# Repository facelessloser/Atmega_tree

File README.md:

# Atmega_tree
Xmas decoration powered by a atmega328 with a few ws2812 LED's

WS2812 library - https://github.com/cpldcpu/light_ws2812

Hardware walk thought - https://youtu.be/ifKlebYnPPQ

Blog post - https://facelesstech.wordpress.com/2015/12/17/atmega_tree/

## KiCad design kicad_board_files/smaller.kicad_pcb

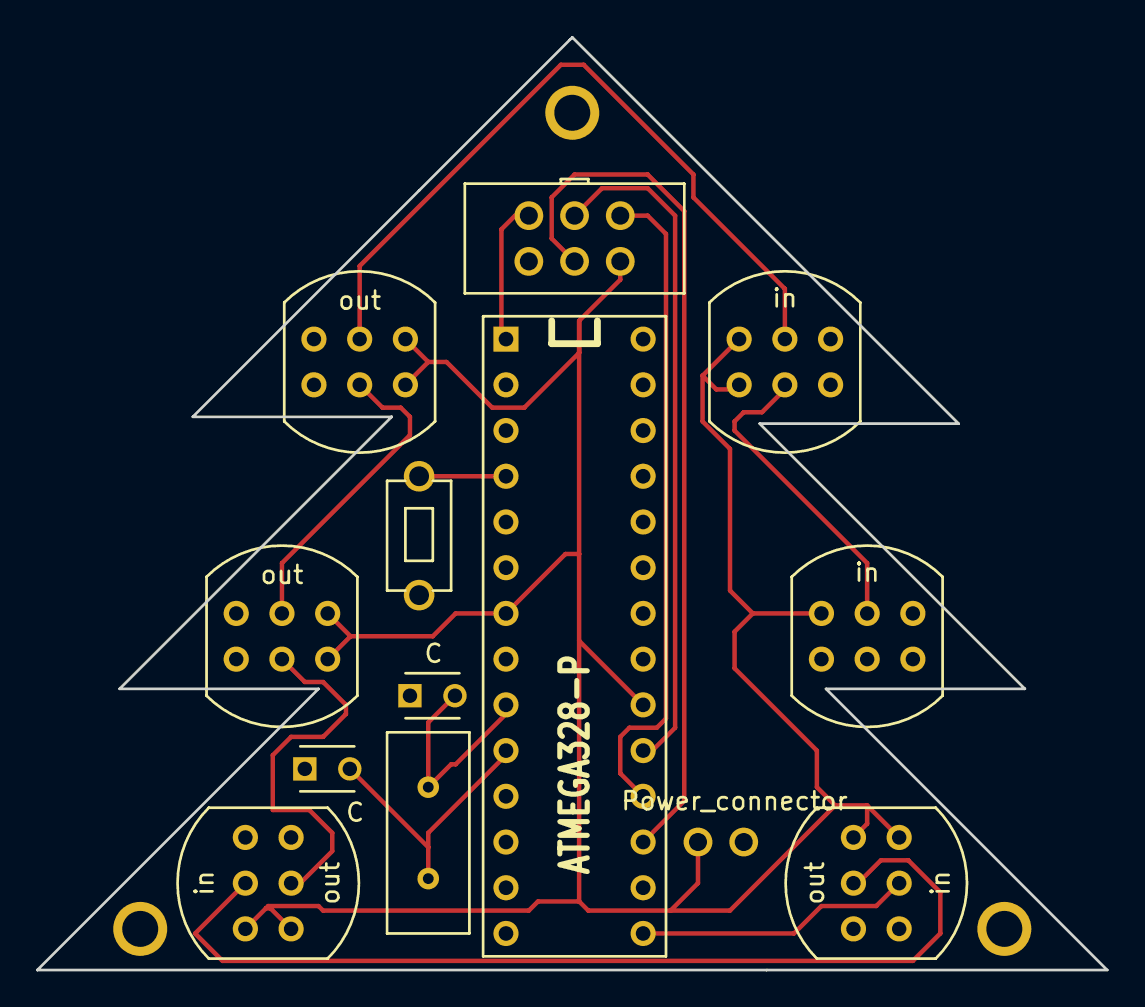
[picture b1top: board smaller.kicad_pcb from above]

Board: 2 copper layers, 59.4 x 51.8 mm, 17 parts (0 on the bottom side), 15 nets.

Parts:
1PIN, 1PIN#2, 1PIN#3: P***; 1pin
C1, C2: C; C_Disc_D3_P2.5
CON1: AVR-ISP-6; IDC_6pin_small_custom
IC1: ATMEGA328-P; atmega328_socket
SW1: SW_PUSH; button_slim_custom
U1: Power_connector
U2, U3, U4, U5, U7, U8: ws2812; ws2812_custom
VAL: OSH_final_silks_back
Y1: Crystal; Crystal_custom

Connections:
GND: C1.1, C2.1, CON1.6, IC1.8, IC1.22, SW1.2, U1.1, U2.1, U2.4, U3.1, U3.4, U4.1, U4.4, U5.1, U5.4, U7.1, U7.4, U8.1
unnamed: C1.2, IC1.9, Y1.2
unnamed: C2.2, IC1.10, Y1.1
unnamed: CON1.1, IC1.18
unnamed: CON1.3, IC1.19
unnamed: CON1.4, IC1.17
unnamed: CON1.5, IC1.1
unnamed: IC1.4, SW1.1
unnamed: IC1.15, U2.2
unnamed: U2.5, U3.2
unnamed: U3.5, U4.2
unnamed: U4.5, U5.2
unnamed: U5.5, U7.2
unnamed: U7.5, U8.2
VCC: CON1.2, IC1.7, IC1.20, U1.2, U2.3, U2.6, U3.3, U3.6, U4.3, U4.6, U5.3, U5.6, U7.3, U7.6, U8.3

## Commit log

2015-11-05 basic starter code, still need to flush out the different modes
2015-11-05 Fixed a bug in the array code
2015-11-18 added new flash sequences and cleaned up the code a lot
2015-12-17 Gerber files for atmega_tree
2015-12-17 added links to blog post and videos
2016-09-24 Added board files
2016-11-01 fixed the millis() wait code to work correctly
2017-02-26 added schmatics
